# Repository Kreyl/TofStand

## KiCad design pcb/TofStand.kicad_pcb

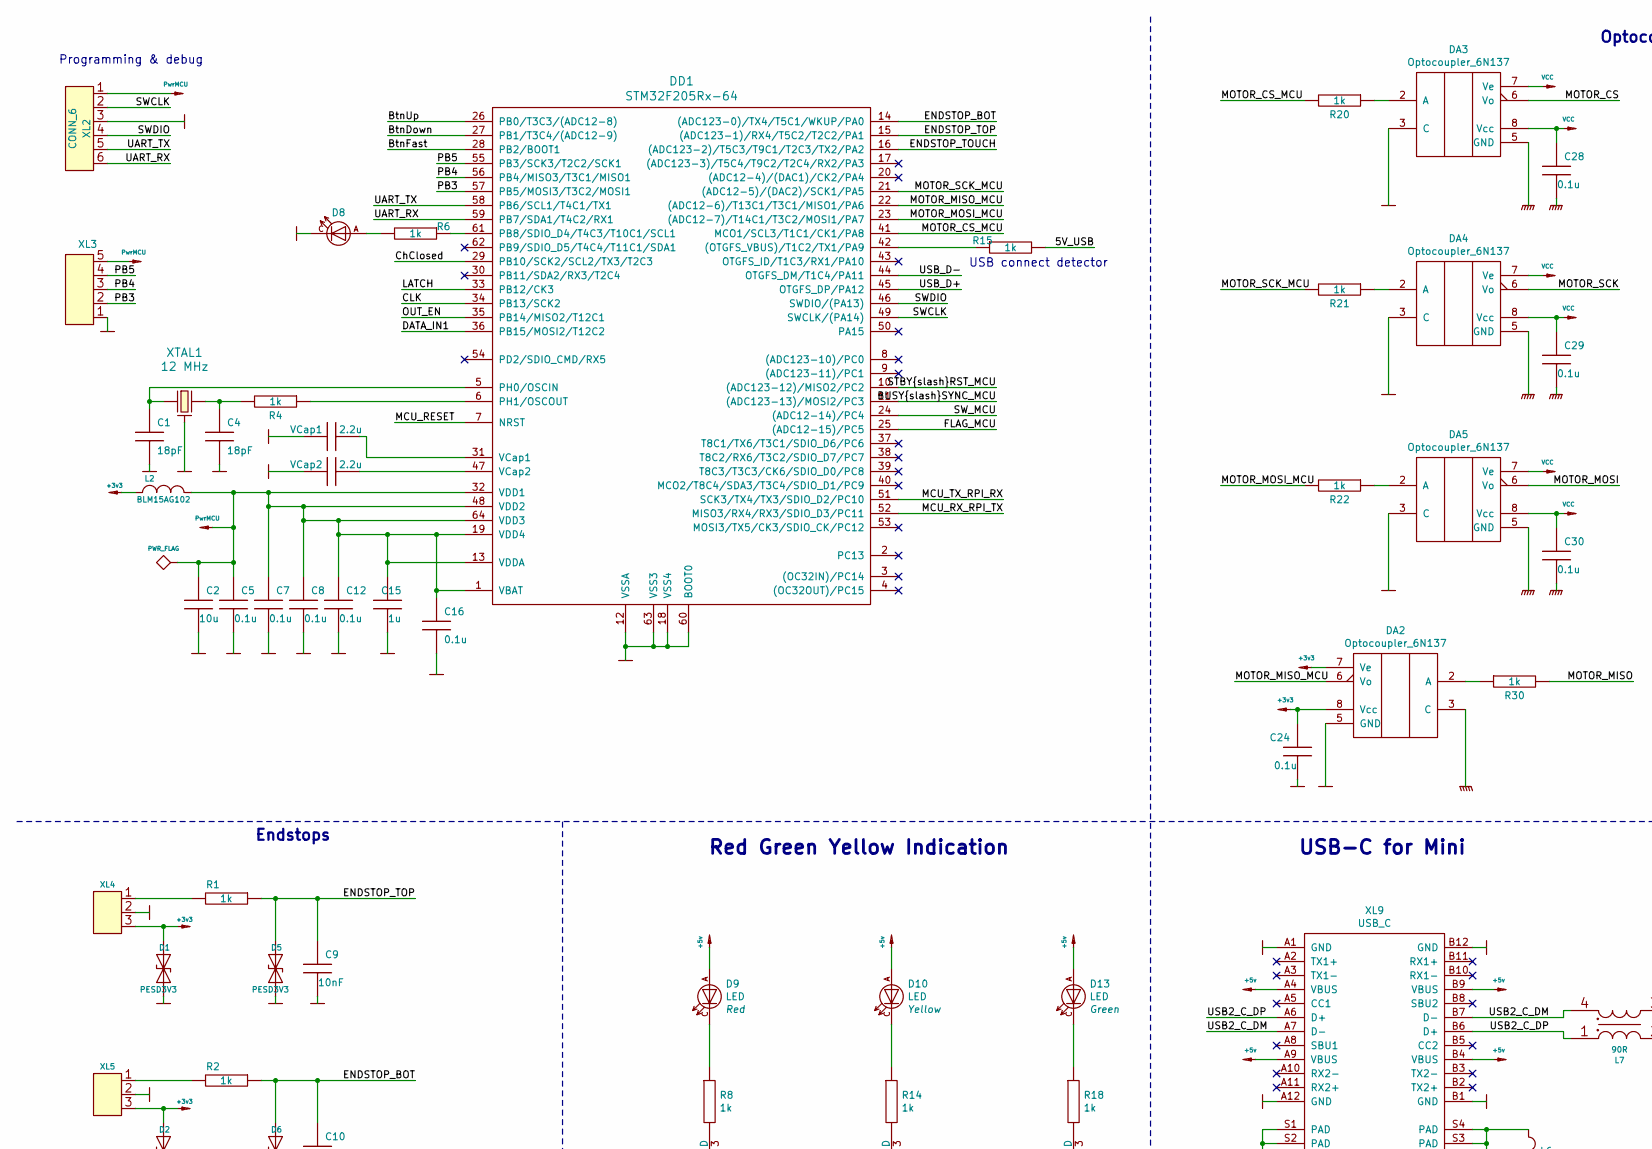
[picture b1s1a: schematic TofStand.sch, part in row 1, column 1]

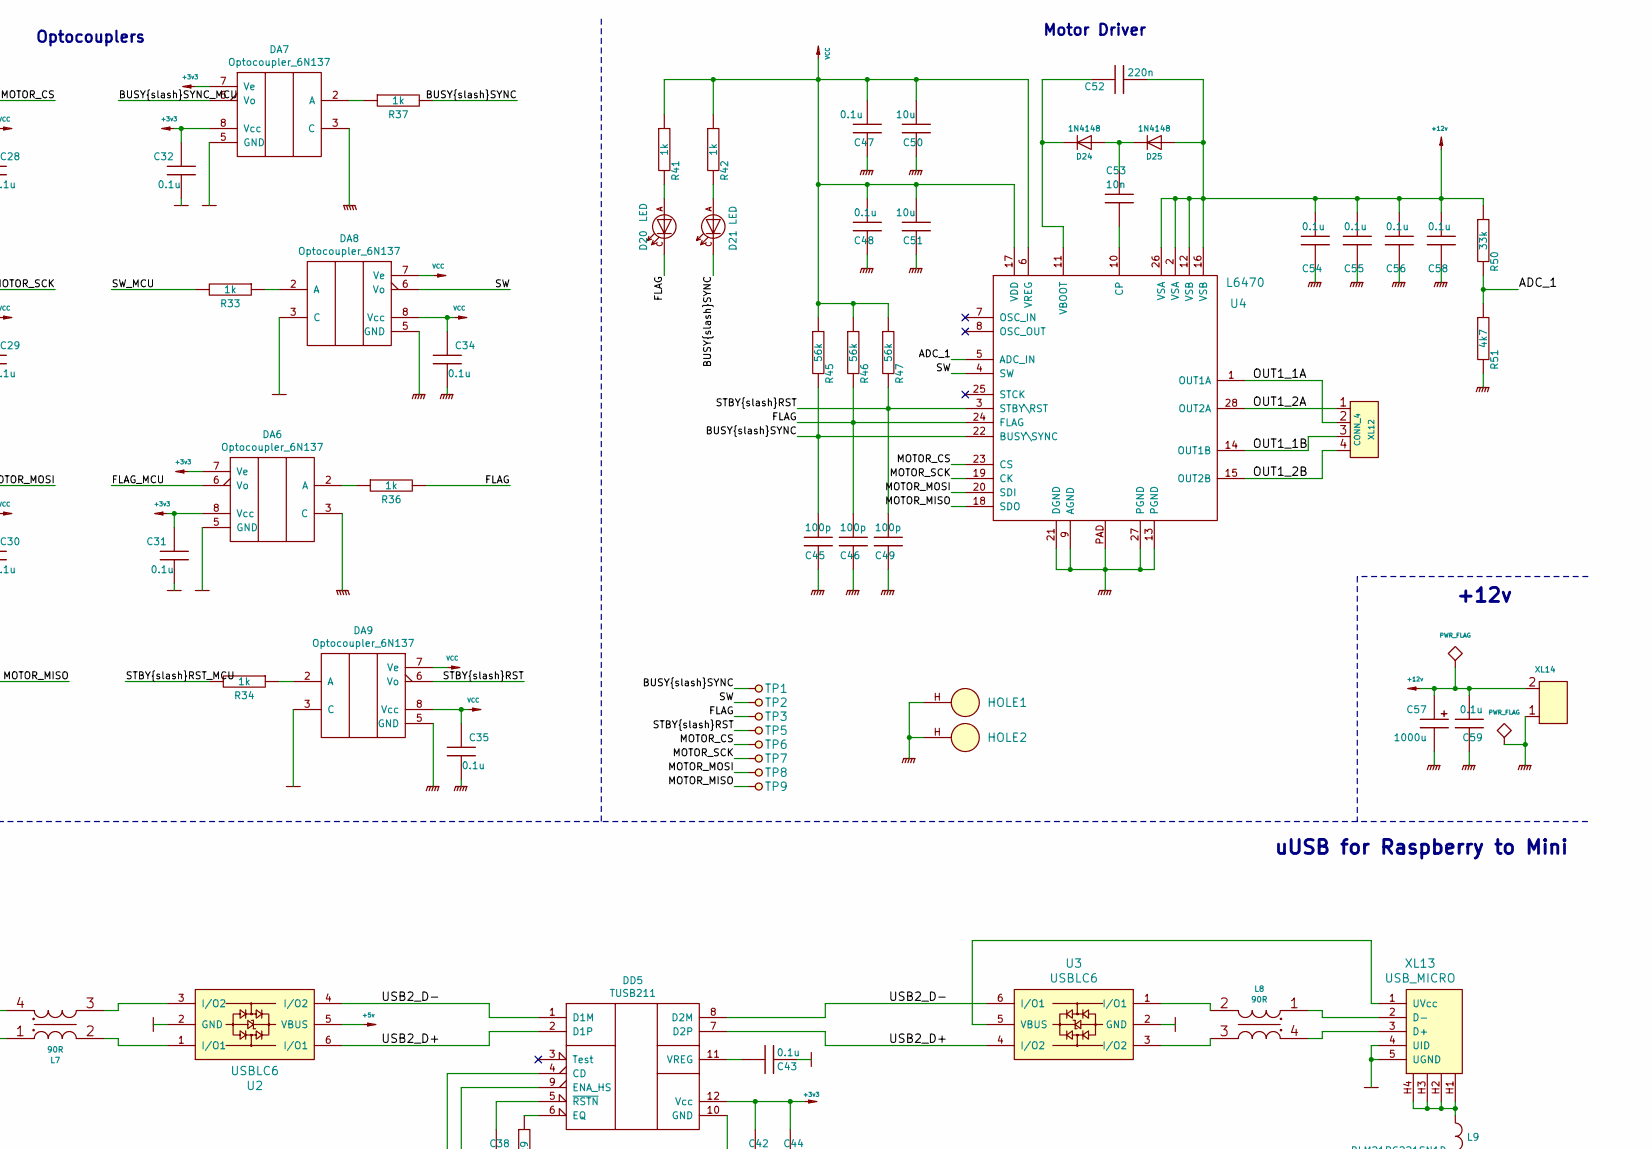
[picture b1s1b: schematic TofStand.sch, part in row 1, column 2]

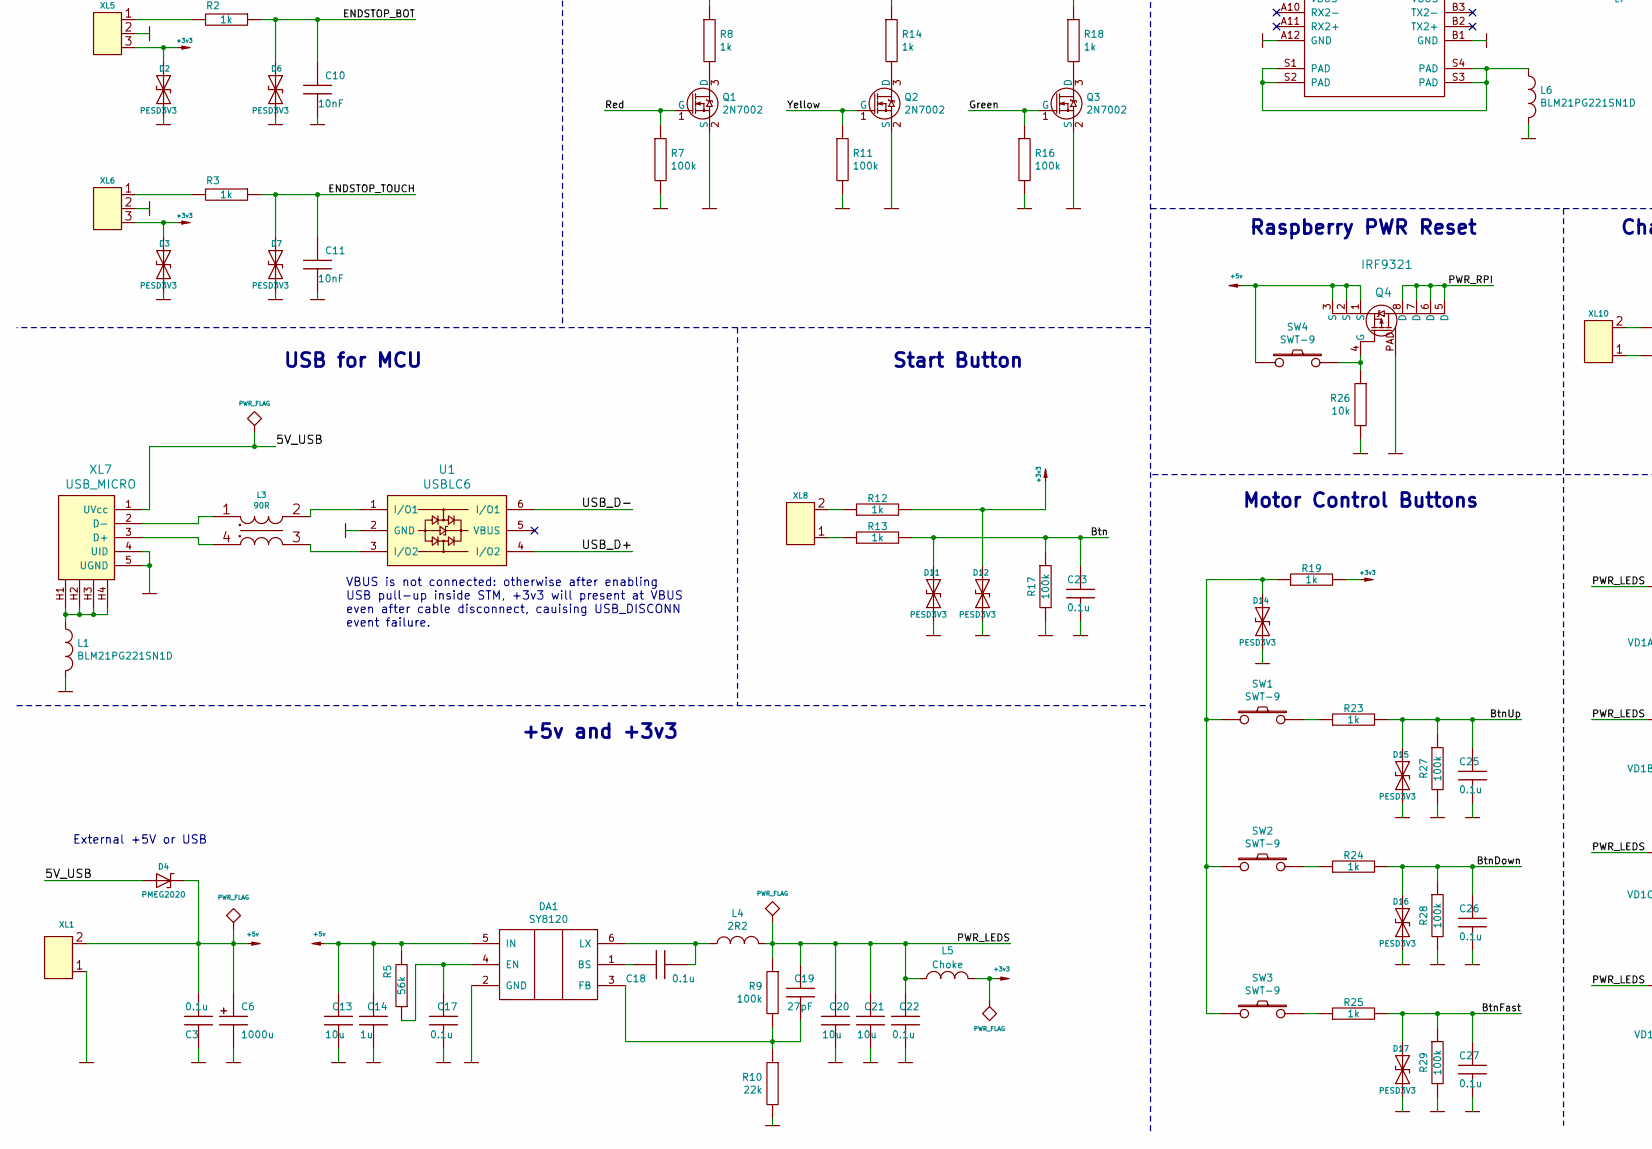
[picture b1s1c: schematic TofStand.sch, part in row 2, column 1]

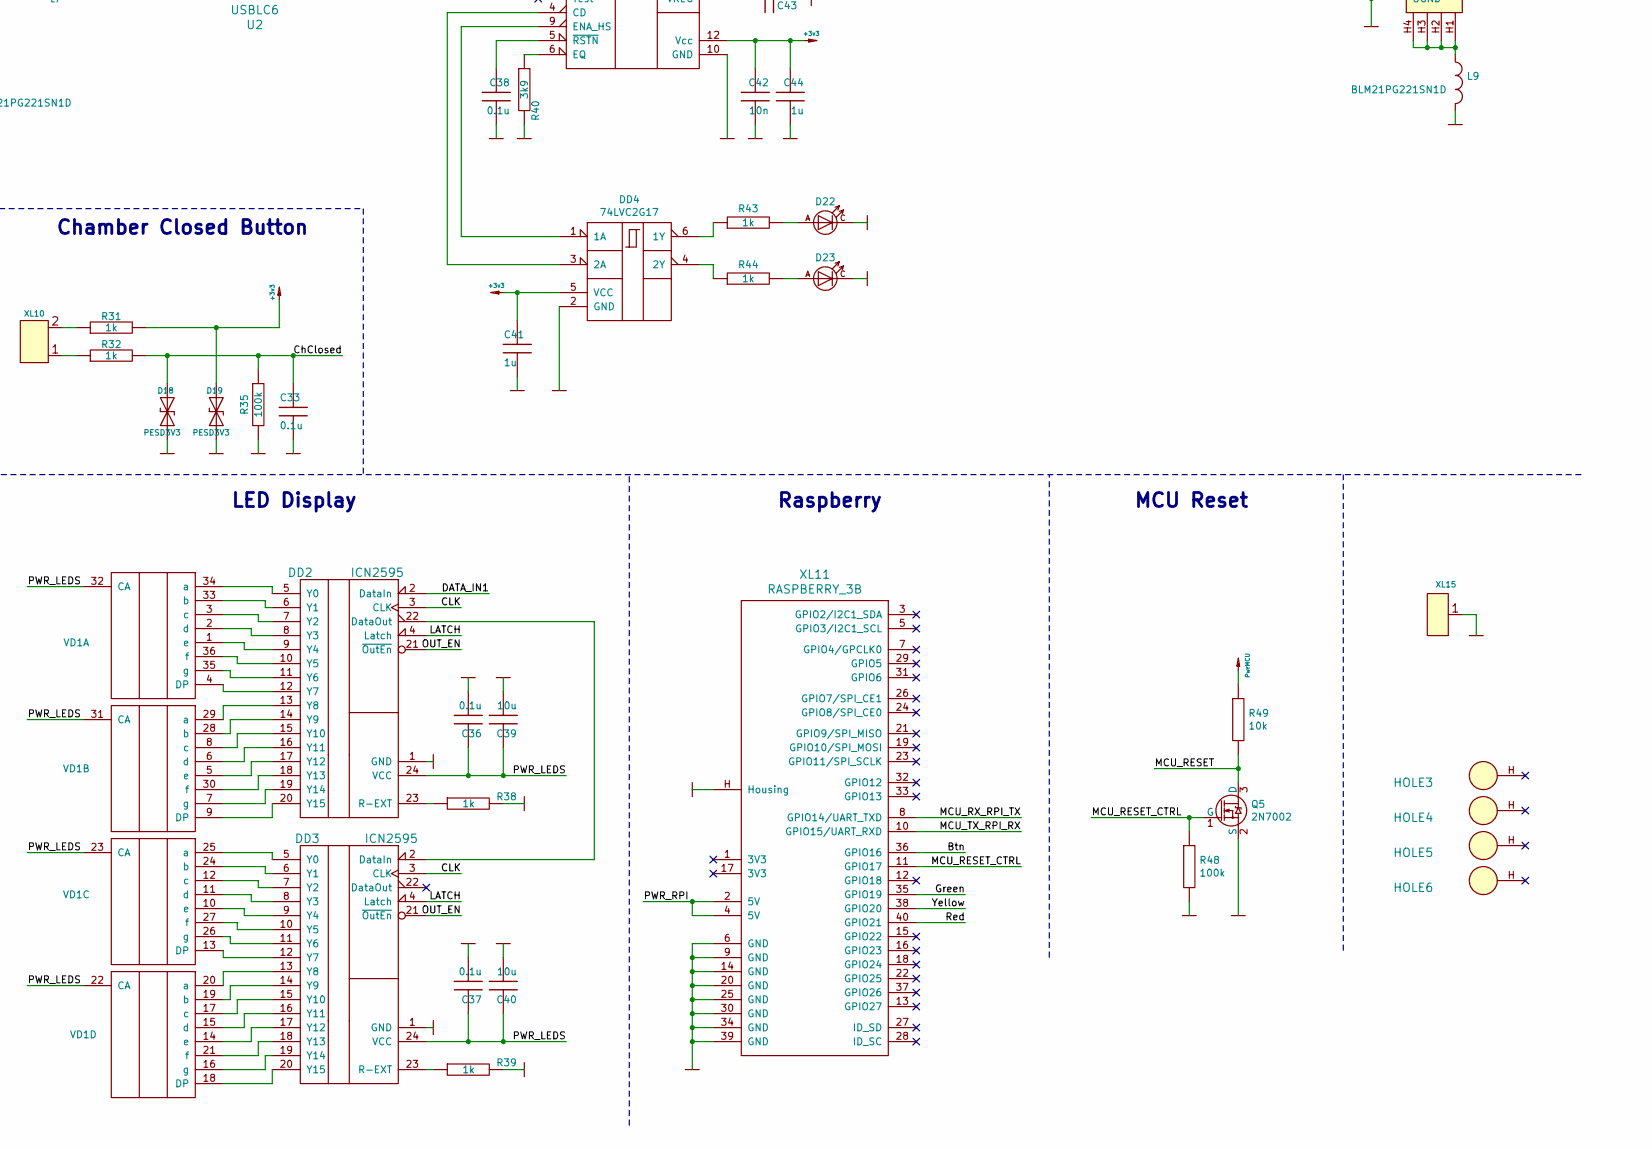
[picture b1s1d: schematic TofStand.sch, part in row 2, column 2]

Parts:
C1, C4: 18pF; CAP_0603_Silks
C2, C13, C20, C21, C39, C40, C50, C51: 10u; CAP_0805
C3, C5, C7, C8, C12, C16, C17, C18, C22, C23, C24, C25, C26, C27, C28, C29, C30, C31, C32, C33, C34, C35, C36, C37, C38, C43, C47, C48, C54, C55, C56, C58, C59: 0.1u; CAP_0603_Silks
C6, C57: 1000u; CAP_10xxR
C9, C10, C11: 10nF; CAP_0603_Silks
C14, C15, C41, C44: 1u; CAP_0603_Silks
C19: 27pF; CAP_0603_Silks
C42, C53: 10n; CAP_0603_Silks
C45, C46, C49: 100p; CAP_0603_Silks
C52: 220n; CAP_0603_Silks
D1, D2, D3, D5, D6, D7, D11, D12, D14, D15, D16, D17, D18, D19: PESD3V3; SOD323
D4: PMEG2020; SOD323
D8, D20, D21, D22, D23: LED; LED_0603
D9, D10, D13: LED; LED_Through-Hole-5mm
D24, D25: 1N4148; SOD80C
DA1: SY8120; SOT23-6
DA2, DA3, DA4, DA5, DA6, DA7, DA8, DA9: Optocoupler_6N137; DIP-8_296_ELL
DD1: STM32F205Rx-64; LQFP64
DD2, DD3: ICN2595; TSSOP24_150_0635
DD4: 74LVC2G17; SOT23-6
DD5: TUSB211; X2QFN_12
HOLE1, HOLE2, HOLE3, HOLE4, HOLE5, HOLE6: HOLE_METALLED; Hole3_5_out6mm
L1, L6, L9: BLM21PG221SN1D; IND_0603
L2: BLM15AG102; IND_0402
L3, L7, L8: 90R; DLW21SN
L4: 2R2; IND_1515
L5: Choke; IND_0402
Q1, Q2, Q3, Q5: 2N7002; SOT23-3
Q4: IRF9321; SO8HEATSINK
R1, R2, R3, R4, R6, R8, R12, R13, R14, R15, R18, R19, R20, R21, R22, R23, R24, R25, R30, R31, R32, R33, R34, R36, R37, R38, R39, R41, R42, R43, R44: 1k; RES_0603
R5, R45, R46, R47: 56k; RES_0603
R7, R9, R11, R16, R17, R27, R28, R29, R35, R48: 100k; RES_0603
R10: 22k; RES_0603
R26, R49: 10k; RES_0603
R40: 3k9; RES_0603
R50: 33k; RES_0603
R51: 4k7; RES_0603
SW1, SW2, SW3, SW4: SWT-9; BTN_SWT9
TP1, TP2, TP3, TP5, TP6, TP7, TP8, TP9: TESTPOINT; TESTPOINT_1MM
U1, U2, U3: USBLC6; SOT23-6
U4: L6470; HTSSOP28
VCap1, VCap2: 2.2u; CAP_0603_Silks
VD1: 7SEGx4_CA; 7Segx4
XL1, XL14: CONN_2; 2ZHDRC-02P
XL2: CONN_6; PLS-6_LOCK
XL3: CONN_5; PLS-5
XL4, XL5, XL6: CONN_3; W03_Pitch_2d54
XL7, XL13: USB_MICRO; USBmicro_MOLEX_1050170001
XL8, XL10: CONN_2; WB-02(MW-2M)
XL9: USB_C; USB_C_MOLEX_1054500101
XL11: RASPBERRY_3B; RaspberryPi3
XL12: CONN_4; TermiBlockHeader_508_x4_R
XL15: CONN_1; PLS-1Rnd
XTAL1: 12 MHz; 03225C4

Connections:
+3v3: C24.1, C31.1, C32.1, C41.2, C42.2, C44.2, D1.C, D2.C, D3.C, D12.C, D19.C, DA2.7 (Ve), DA2.8 (Vcc), DA6.7 (Ve), DA6.8 (Vcc), DA7.7 (Ve), DA7.8 (Vcc), DD4.5 (VCC), DD5.12 (Vcc), L2.2, L5.1, R12.2, R19.2, R31.2, XL4.3, XL5.3, XL6.3
+5v: C3.1, C6.1, C13.1, C14.1, D4.C, D9.A, D10.A, D13.A, DA1.5 (IN), Q4.1 (S), Q4.2 (S), Q4.3 (S), R5.2, SW4.1, U2.5 (VBUS), XL1.2 (PM), XL9.A4 (VBUS), XL9.A9 (VBUS), XL9.B4 (VBUS), XL9.B9 (VBUS)
+12v: C52.2, C54.1, C55.1, C56.1, C57.1, C58.1, C59.1, D25.A, R50.1, U4.2 (VSA), U4.12 (VSB), U4.16 (VSB), U4.26 (VSA), XL14.2 (PM)
/5V_USB: D4.A, R15.2, XL7.1 (UVcc)
/ADC_1: R50.2, R51.1, U4.5 (ADC_IN)
/BUSY/SYNC: C45.1, D21.C, R37.2, R45.2, TP1.1, U4.22 (BUSY\SYNC)
/BUSY/SYNC_MCU: DA7.6 (Vo), DD1.11 ((ADC123-13)/MOSI2/PC3)
/Btn: C23.1, D11.C, R13.2, R17.1, XL11.36 (GPIO16)
/BtnDown: C26.1, D16.C, DD1.27 (PB1/T3C4/(ADC12-9)), R24.2, R28.1
/BtnFast: C27.1, D17.C, DD1.28 (PB2/BOOT1), R25.2, R29.1
/BtnUp: C25.1, D15.C, DD1.26 (PB0/T3C3/(ADC12-8)), R23.2, R27.1
/CLK: DD1.34 (PB13/SCK2), DD2.3 (CLK), DD3.3 (CLK)
/ChClosed: C33.1, D18.C, DD1.29 (PB10/SCK2/SCL2/TX3/T2C3), R32.2, R35.1
/DATA_IN1: DD1.36 (PB15/MOSI2/T12C2), DD2.2 (DataIn)
/ENDSTOP_BOT: C10.1, D6.C, DD1.14 ((ADC123-0)/TX4/T5C1/WKUP/PA0), R2.1
/ENDSTOP_TOP: C9.1, D5.C, DD1.15 ((ADC123-1)/RX4/T5C2/T2C2/PA1), R1.1
/ENDSTOP_TOUCH: C11.1, D7.C, DD1.16 ((ADC123-2)/T5C3/T9C1/T2C3/TX2/PA2), R3.1
/FLAG: C46.1, D20.C, R36.2, R46.2, TP3.1, U4.24 (FLAG)
/FLAG_MCU: DA6.6 (Vo), DD1.25 ((ADC12-15)/PC5)
/Green: Q3.1 (G), R16.1, XL11.35 (GPIO19)
/LATCH: DD1.33 (PB12/CK3), DD2.4 (Latch), DD3.4 (Latch)
/MCU_RESET: DD1.7 (NRST), Q5.3 (D), R49.2
/MCU_RESET_CTRL: Q5.1 (G), R48.1, XL11.11 (GPIO17)
/MCU_RX_RPI_TX: DD1.52 (MISO3/RX4/RX3/SDIO_D3/PC11), XL11.8 (GPIO14/UART_TXD)
/MCU_TX_RPI_RX: DD1.51 (SCK3/TX4/TX3/SDIO_D2/PC10), XL11.10 (GPIO15/UART_RXD)
/MOTOR_CS: DA3.6 (Vo), TP6.1, U4.23 (CS)
/MOTOR_CS_MCU: DD1.41 (MCO1/SCL3/T1C1/CK1/PA8), R20.2
/MOTOR_MISO: R30.2, TP9.1, U4.18 (SDO)
/MOTOR_MISO_MCU: DA2.6 (Vo), DD1.22 ((ADC12-6)/T13C1/T3C1/MISO1/PA6)
/MOTOR_MOSI: DA5.6 (Vo), TP8.1, U4.20 (SDI)
/MOTOR_MOSI_MCU: DD1.23 ((ADC12-7)/T14C1/T3C2/MOSI1/PA7), R22.2
/MOTOR_SCK: DA4.6 (Vo), TP7.1, U4.19 (CK)
/MOTOR_SCK_MCU: DD1.21 ((ADC12-5)/(DAC2)/SCK1/PA5), R21.2
/OUT1_1A: U4.1 (OUT1A), XL12.2 (PM)
/OUT1_1B: U4.14 (OUT1B), XL12.3
/OUT1_2A: U4.28 (OUT2A), XL12.1
/OUT1_2B: U4.15 (OUT2B), XL12.4
/OUT_EN: DD1.35 (PB14/MISO2/T12C1), DD2.21 (~OutEn), DD3.21 (~OutEn)
/PB3: DD1.57 (PB5/MOSI3/T3C2/MOSI1), XL3.2
/PB4: DD1.56 (PB4/MISO3/T3C1/MISO1), XL3.3
/PB5: DD1.55 (PB3/SCK3/T2C2/SCK1), XL3.4
/PWR_LEDS: C19.1, C20.1, C21.1, C22.1, C36.2, C37.2, C39.2, C40.2, DD2.24 (VCC), DD3.24 (VCC), L4.2, L5.2, R9.1, VD1.22 (CA), VD1.23 (CA), VD1.31 (CA), VD1.32 (CA)
/PWR_RPI: Q4.5 (D), Q4.6 (D), Q4.7 (D), Q4.8 (D), XL11.2 (5V), XL11.4 (5V)
/Red: Q1.1 (G), R7.1, XL11.40 (GPIO21)
/STBY/RST: C49.1, DA9.6 (Vo), R47.2, TP5.1, U4.3 (STBY\RST)
/STBY/RST_MCU: DD1.10 ((ADC123-12)/MISO2/PC2), R34.2
/SW: DA8.6 (Vo), TP2.1, U4.4 (SW)
/SWCLK: DD1.49 (SWCLK/(PA14)), XL2.2
/SWDIO: DD1.46 (SWDIO/(PA13)), XL2.4
/SW_MCU: DD1.24 ((ADC12-14)/PC4), R33.2
/UART_RX: DD1.59 (PB7/SDA1/T4C2/RX1), XL2.6
/UART_TX: DD1.58 (PB6/SCL1/T4C1/TX1), XL2.5
/USB2_C_DM: L7.4, XL9.A7 (D-), XL9.B7 (D-)
/USB2_C_DP: L7.1, XL9.A6 (D+), XL9.B6 (D+)
/USB2_D+: DD5.2 (D1P), DD5.7 (D2P), U2.6 (I/O1), U3.4 (I/O2)
/USB2_D-: DD5.1 (D1M), DD5.8 (D2M), U2.4 (I/O2), U3.6 (I/O1)
/USB_D+: DD1.45 (OTGFS_DP/PA12), U1.4 (I/O2)
/USB_D-: DD1.44 (OTGFS_DM/T1C4/PA11), U1.6 (I/O1)
/Yellow: Q2.1 (G), R11.1, XL11.38 (GPIO20)
GND: C1.2, C2.2, C3.2, C4.2, C5.2, C6.2, C7.2, C8.2, C9.2, C10.2, C11.2, C12.2, C13.2, C14.2, C15.2, C16.2, C17.2, C20.2, C21.2, C22.2, C23.2, C24.2, C25.2, C26.2, C27.2, C31.2, C32.2, C33.2, C36.1, C37.1, C38.1, C39.1, C40.1, C41.1, C42.1, C43.1, C44.1, D1.A, D2.A, D3.A, D5.A, D6.A, D7.A, D8.C, D11.A, D12.A, D14.A, D15.A, D16.A, D17.A, D18.A, D19.A, D22.C, D23.C, DA1.2 (GND), DA2.5 (GND), DA3.3 (C), DA4.3 (C), DA5.3 (C), DA6.5 (GND), DA7.5 (GND), DA8.3 (C), DA9.3 (C), DD1.12 (VSSA), DD1.18 (VSS4), DD1.60 (BOOT0), DD1.63 (VSS3), DD2.1 (GND), DD3.1 (GND), DD4.2 (GND), DD5.10 (GND), L1.2, L6.2, L9.2, Q1.2 (S), Q2.2 (S), Q3.2 (S), Q4.PAD, Q5.2 (S), R7.2, R10.2, R11.2, R16.2, R17.2, R26.2, R27.2, R28.2, R29.2, R35.2, R38.2, R39.2, R40.2, R48.2, U1.2 (GND), U2.2 (GND), U3.2 (GND), VCap1.2, VCap2.2, XL1.1, XL2.3, XL3.1, XL4.2 (PM), XL5.2 (PM), XL6.2 (PM), XL7.4 (UID), XL7.5 (UGND), XL9.A1 (GND), XL9.A12 (GND), XL9.B1 (GND), XL9.B12 (GND), XL11.6 (GND), XL11.9 (GND), XL11.14 (GND), XL11.20 (GND), XL11.25 (GND), XL11.30 (GND), XL11.34 (GND)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
GNDPWR: C28.2, C29.2, C30.2, C34.2, C35.2, C45.2, C46.2, C47.2, C48.2, C49.2, C50.2, C51.2, C54.2, C55.2, C56.2, C57.2, C58.2, C59.2, DA2.3 (C), DA3.5 (GND), DA4.5 (GND), DA5.5 (GND), DA6.3 (C), DA7.3 (C), DA8.5 (GND), DA9.5 (GND), HOLE1.H, HOLE2.H, R51.2, U4.9 (AGND), U4.13 (PGND), U4.21 (DGND), U4.27 (PGND), U4.PAD, XL14.1
unnamed: C1.1, DD1.5 (PH0/OSCIN), XTAL1.1
unnamed: C4.1, R4.2, XTAL1.2
unnamed: C17.1, DA1.4 (EN), R5.1
unnamed: C18.1, DA1.1 (BS)
unnamed: C18.2, DA1.6 (LX), L4.1
unnamed: C19.2, DA1.3 (FB), R9.2, R10.1
unnamed: C52.1, D24.C, U4.11 (VBOOT)
unnamed: C53.1, D24.A, D25.C
unnamed: C53.2, U4.10 (CP)
unnamed: C38.2, DD5.5 (~RSTN)
unnamed: C43.2, DD5.11 (VREG)
unnamed: D8.A, R6.2
unnamed: D9.C, R8.1
unnamed: D10.C, R14.1
unnamed: D13.C, R18.1
unnamed: D14.C, R19.1, SW1.1, SW2.1, SW3.1
unnamed: D20.A, R41.2
unnamed: D21.A, R42.2
unnamed: D22.A, R43.2
unnamed: D23.A, R44.2
unnamed: DA2.2 (A), R30.1
unnamed: DA3.2 (A), R20.1
unnamed: DA4.2 (A), R21.1
unnamed: DA5.2 (A), R22.1
unnamed: DA6.2 (A), R36.1
unnamed: DA7.2 (A), R37.1
unnamed: DA8.2 (A), R33.1
unnamed: DA9.2 (A), R34.1
unnamed: DD1.6 (PH1/OSCOUT), R4.1
unnamed: DD1.31 (VCap1), VCap1.1
unnamed: DD1.42 ((OTGFS_VBUS)/T1C2/TX1/PA9), R15.1
unnamed: DD1.47 (VCap2), VCap2.1
unnamed: DD1.61 (PB8/SDIO_D4/T4C3/T10C1/SCL1), R6.1
unnamed: DD2.22 (DataOut), DD3.2 (DataIn)
unnamed: DD3.5 (Y0), VD1.25 (a)
unnamed: DD3.6 (Y1), VD1.24 (b)
unnamed: DD3.7 (Y2), VD1.12 (c)
unnamed: DD3.8 (Y3), VD1.11 (d)
unnamed: DD3.9 (Y4), VD1.10 (e)
unnamed: DD3.10 (Y5), VD1.27 (f)
unnamed: DD3.11 (Y6), VD1.26 (g)
unnamed: DD3.12 (Y7), VD1.13 (DP)
unnamed: DD3.13 (Y8), VD1.20 (a)
unnamed: DD3.14 (Y9), VD1.19 (b)
unnamed: DD3.15 (Y10), VD1.17 (c)
unnamed: DD3.16 (Y11), VD1.15 (d)
unnamed: DD3.17 (Y12), VD1.14 (e)
unnamed: DD3.18 (Y13), VD1.21 (f)
unnamed: DD3.19 (Y14), VD1.16 (g)
unnamed: DD3.20 (Y15), VD1.18 (DP)
unnamed: DD3.23 (R-EXT), R39.1
unnamed: DD4.1 (1A), DD5.9 (ENA_HS)
unnamed: DD4.3 (2A), DD5.4 (CD)
unnamed: DD4.4 (2Y), R44.1
unnamed: DD2.5 (Y0), VD1.34 (a)
unnamed: DD4.6 (1Y), R43.1
unnamed: DD2.6 (Y1), VD1.33 (b)
unnamed: DD2.7 (Y2), VD1.3 (c)
unnamed: DD2.8 (Y3), VD1.2 (d)
unnamed: DD2.9 (Y4), VD1.1 (e)
unnamed: DD2.10 (Y5), VD1.36 (f)
unnamed: DD2.11 (Y6), VD1.35 (g)
unnamed: DD2.12 (Y7), VD1.4 (DP)
unnamed: DD2.13 (Y8), VD1.29 (a)
unnamed: DD2.14 (Y9), VD1.28 (b)
unnamed: DD2.15 (Y10), VD1.8 (c)
unnamed: DD2.16 (Y11), VD1.6 (d)
unnamed: DD2.17 (Y12), VD1.5 (e)
unnamed: DD2.18 (Y13), VD1.30 (f)
unnamed: DD2.19 (Y14), VD1.7 (g)
unnamed: DD2.20 (Y15), VD1.9 (DP)
unnamed: DD2.23 (R-EXT), R38.1
unnamed: DD5.6 (EQ), R40.1
unnamed: L3.1, XL7.2 (D-)
unnamed: L1.1, XL7.H1, XL7.H2, XL7.H3, XL7.H4
unnamed: L3.2, U1.1 (I/O1)
unnamed: L3.3, U1.3 (I/O2)
unnamed: L3.4, XL7.3 (D+)
unnamed: L6.1, XL9.S1 (PAD), XL9.S2 (PAD), XL9.S3 (PAD), XL9.S4 (PAD)
unnamed: L7.2, U2.1 (I/O1)
unnamed: L7.3, U2.3 (I/O2)
unnamed: L8.1, XL13.2 (D-)
unnamed: L8.2, U3.1 (I/O1)
unnamed: L8.3, U3.3 (I/O2)
unnamed: L8.4, XL13.3 (D+)
unnamed: L9.1, XL13.H1, XL13.H2, XL13.H3, XL13.H4
unnamed: Q1.3 (D), R8.2
unnamed: Q2.3 (D), R14.2
unnamed: Q3.3 (D), R18.2
unnamed: Q4.4 (G), R26.1, SW4.2
unnamed: R1.2, XL4.1
unnamed: R2.2, XL5.1
unnamed: R3.2, XL6.1
unnamed: R13.1, XL8.1
unnamed: R12.1, XL8.2 (PM)
unnamed: R23.1, SW1.2
unnamed: R24.1, SW2.2
unnamed: R25.1, SW3.2
unnamed: R31.1, XL10.2 (PM)
unnamed: R32.1, XL10.1
unnamed: U3.5 (VBUS), XL13.1 (UVcc)
PwrMCU: C2.1, C5.1, C7.1, C8.1, C12.1, C15.1, C16.1, DD1.1 (VBAT), DD1.13 (VDDA), DD1.19 (VDD4), DD1.32 (VDD1), DD1.48 (VDD2), DD1.64 (VDD3), L2.1, R49.1, XL2.1, XL3.5
VCC: C28.1, C29.1, C30.1, C34.1, C35.1, C47.1, C48.1, C50.1, C51.1, DA3.7 (Ve), DA3.8 (Vcc), DA4.7 (Ve), DA4.8 (Vcc), DA5.7 (Ve), DA5.8 (Vcc), DA8.7 (Ve), DA8.8 (Vcc), DA9.7 (Ve), DA9.8 (Vcc), R41.1, R42.1, R45.1, R46.1, R47.1, U4.6 (VREG), U4.17 (VDD)

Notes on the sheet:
VBUS is not connected: otherwise after enabling USB pull-up inside STM, +3v3 will present at VBUS even after cable disconnect, cauising USB_DISCONN event failure.
USB for MCU
USB connect detector
Programming & debug
Endstops
Red Green Yellow Indication
Optocouplers
Motor Driver
Start Button
uUSB for Raspberry to Mini
+5v and +3v3
USB-C for Mini
+12v
Motor Control Buttons
Raspberry
LED Display
MCU Reset
External +5V or USB
Raspberry PWR Reset
Chamber Closed Button

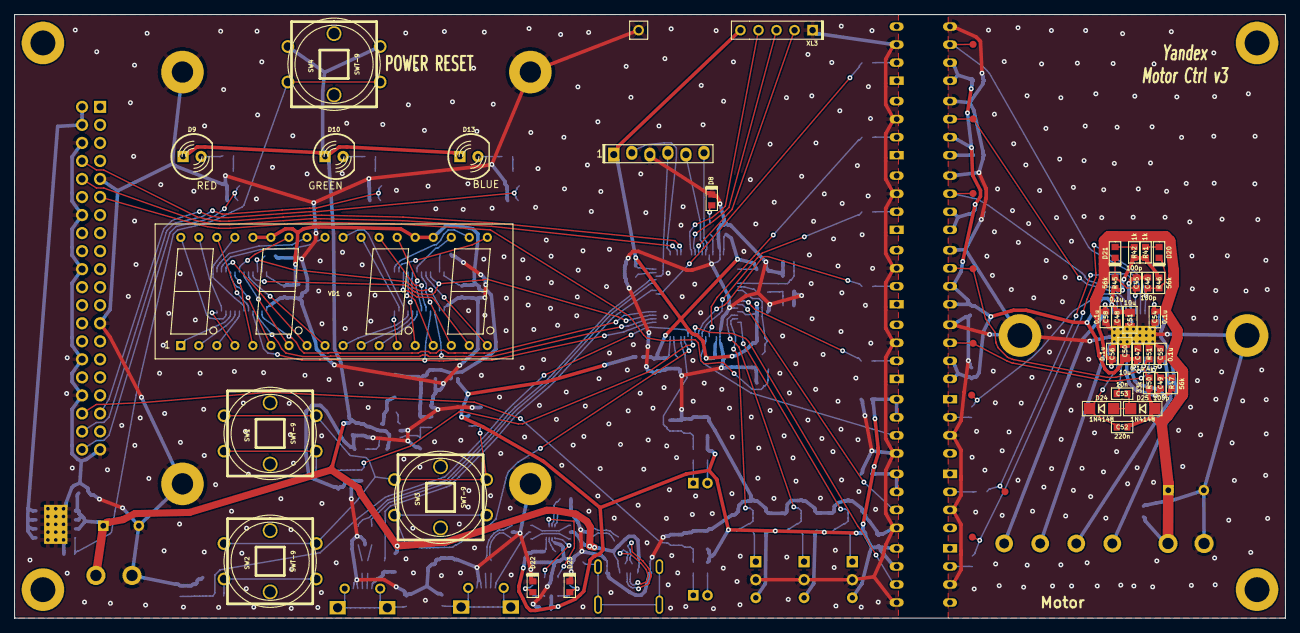
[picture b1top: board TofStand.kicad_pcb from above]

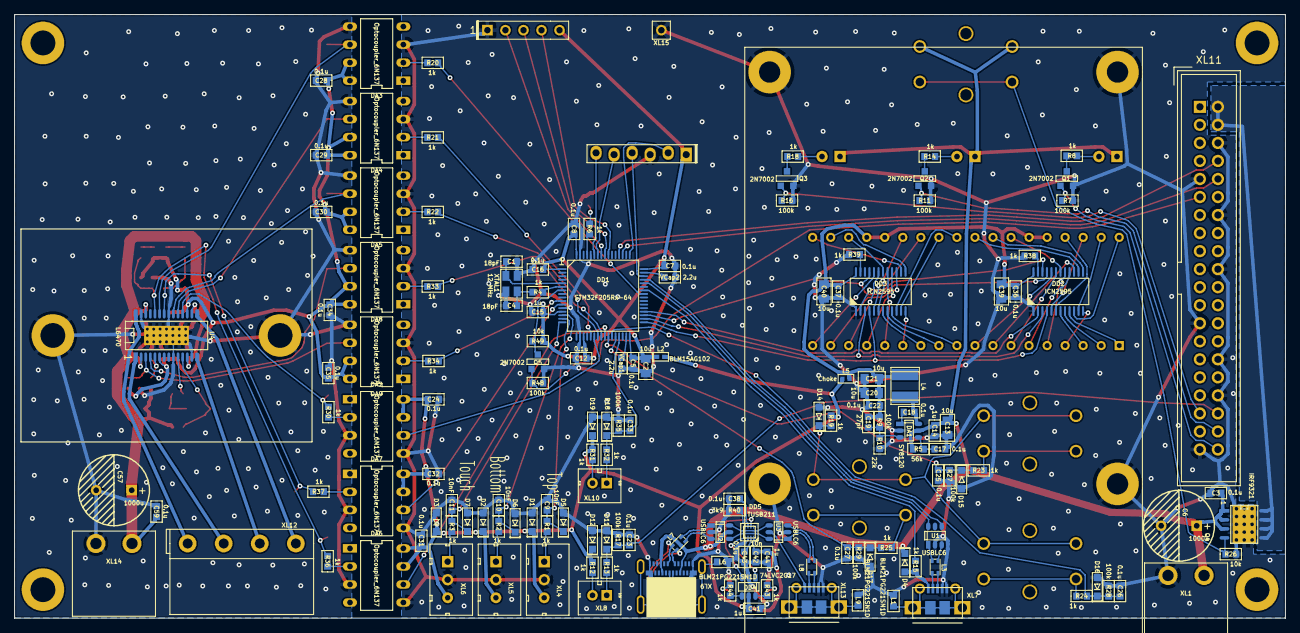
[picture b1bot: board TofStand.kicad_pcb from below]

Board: 2 copper layers, 179.0 x 85.0 mm, 204 parts (153 on the bottom side), 164 nets.

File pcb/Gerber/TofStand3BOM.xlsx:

Ref | Value | Footprint | Datasheet | Manufacturer | Vendor
C1 | 18pF | Capacitors:CAP_0603_Silks
C2 | 10u | Capacitors:CAP_0805
C3 | 0.1u | Capacitors:CAP_0603_Silks | ~
C4 | 18pF | Capacitors:CAP_0603_Silks
C5 | 0.1u | Capacitors:CAP_0603_Silks
C6 | 1000u | Capacitors:CAP_10xxR
C7 | 0.1u | Capacitors:CAP_0603_Silks
C8 | 0.1u | Capacitors:CAP_0603_Silks
C9 | 10nF | Capacitors:CAP_0603_Silks
C10 | 10nF | Capacitors:CAP_0603_Silks
C11 | 10nF | Capacitors:CAP_0603_Silks
C12 | 0.1u | Capacitors:CAP_0603_Silks
C13 | 10u | Capacitors:CAP_0805
C14 | 1u | Capacitors:CAP_0603_Silks
C15 | 1u | Capacitors:CAP_0603_Silks
C16 | 0.1u | Capacitors:CAP_0603_Silks
C17 | 0.1u | Capacitors:CAP_0603_Silks
C18 | 0.1u | Capacitors:CAP_0603_Silks
C19 | 27pF | Capacitors:CAP_0603_Silks
C20 | 10u | Capacitors:CAP_0805
C21 | 10u | Capacitors:CAP_0805
C22 | 0.1u | Capacitors:CAP_0603_Silks
C23 | 0.1u | Capacitors:CAP_0603_Silks
C24 | 0.1u | Capacitors:CAP_0603_Silks
C25 | 0.1u | Capacitors:CAP_0603_Silks
C26 | 0.1u | Capacitors:CAP_0603_Silks
C27 | 0.1u | Capacitors:CAP_0603_Silks
C28 | 0.1u | Capacitors:CAP_0603_Silks
C29 | 0.1u | Capacitors:CAP_0603_Silks
C30 | 0.1u | Capacitors:CAP_0603_Silks
C31 | 0.1u | Capacitors:CAP_0603_Silks
C32 | 0.1u | Capacitors:CAP_0603_Silks
C33 | 0.1u | Capacitors:CAP_0603_Silks
C34 | 0.1u | Capacitors:CAP_0603_Silks
C35 | 0.1u | Capacitors:CAP_0603_Silks
C36 | 0.1u | Capacitors:CAP_0603_Silks
C37 | 0.1u | Capacitors:CAP_0603_Silks
C38 | 0.1u | Capacitors:CAP_0603_Silks
C39 | 10u | Capacitors:CAP_0805
C40 | 10u | Capacitors:CAP_0805
C41 | 1u | Capacitors:CAP_0603_Silks
C42 | 10n | Capacitors:CAP_0603_Silks
C43 | 0.1u | Capacitors:CAP_0603_Silks
C44 | 1u | Capacitors:CAP_0603_Silks
C45 | 100p | Capacitors:CAP_0603_Silks | ~
C46 | 100p | Capacitors:CAP_0603_Silks | ~
C47 | 0.1u | Capacitors:CAP_0603_Silks | ~
C48 | 0.1u | Capacitors:CAP_0603_Silks | ~
C49 | 100p | Capacitors:CAP_0603_Silks | ~
C50 | 10u | Capacitors:CAP_0805 | ~
C51 | 10u | Capacitors:CAP_0805 | ~
C52 | 220n | Capacitors:CAP_0603_Silks | ~
C53 | 10n | Capacitors:CAP_0603_Silks | ~
C54 | 0.1u | Capacitors:CAP_0603_Silks | ~
C55 | 0.1u | Capacitors:CAP_0603_Silks | ~
C56 | 0.1u | Capacitors:CAP_0603_Silks | ~
C57 | 1000u | Capacitors:CAP_10xxR
C58 | 0.1u | Capacitors:CAP_0603_Silks | ~
C59 | 0.1u | Capacitors:CAP_0603_Silks | ~
D1 | PESD3V3 | Diodes:SOD323
D2 | PESD3V3 | Diodes:SOD323
D3 | PESD3V3 | Diodes:SOD323
D4 | PMEG2020 | Diodes:SOD323
D5 | PESD3V3 | Diodes:SOD323
D6 | PESD3V3 | Diodes:SOD323
D7 | PESD3V3 | Diodes:SOD323
D8 | LED | LEDs:LED_0603
D9 | LED | LEDs:LED_Through-Hole-5mm
D10 | LED | LEDs:LED_Through-Hole-5mm
D11 | PESD3V3 | Diodes:SOD323
D12 | PESD3V3 | Diodes:SOD323
D13 | LED | LEDs:LED_Through-Hole-5mm
D14 | PESD3V3 | Diodes:SOD323
D15 | PESD3V3 | Diodes:SOD323
D16 | PESD3V3 | Diodes:SOD323
D17 | PESD3V3 | Diodes:SOD323
D18 | PESD3V3 | Diodes:SOD323
D19 | PESD3V3 | Diodes:SOD323
D20 | LED | LEDs:LED_0603 | ~
D21 | LED | LEDs:LED_0603 | ~
D22 | LED | LEDs:LED_0603
D23 | LED | LEDs:LED_0603
D24 | 1N4148 | Diodes:SOD80C | ~
D25 | 1N4148 | Diodes:SOD80C | ~
DA1 | SY8120 | SOT:SOT23-6
DA2 | Optocoupler_6N137 | DIP:DIP-8_296_ELL
DA3 | Optocoupler_6N137 | DIP:DIP-8_296_ELL
DA4 | Optocoupler_6N137 | DIP:DIP-8_296_ELL
DA5 | Optocoupler_6N137 | DIP:DIP-8_296_ELL
DA6 | Optocoupler_6N137 | DIP:DIP-8_296_ELL
DA7 | Optocoupler_6N137 | DIP:DIP-8_296_ELL
DA8 | Optocoupler_6N137 | DIP:DIP-8_296_ELL
DA9 | Optocoupler_6N137 | DIP:DIP-8_296_ELL
DD1 | STM32F205Rx-64 | LQFP_TQFP:LQFP64
DD2 | ICN2595 | SO_DIL_TSSOP:TSSOP24_150_0635
DD3 | ICN2595 | SO_DIL_TSSOP:TSSOP24_150_0635
DD4 | 74LVC2G17 | SOT:SOT23-6
DD5 | TUSB211 | QFN_DFN:X2QFN_12
L1 | BLM21PG221SN1D | Inductors:IND_0603
L2 | BLM15AG102 | Inductors:IND_0402
L3 | 90R | Inductors:DLW21SN
L4 | 2R2 | Inductors:IND_1515
L5 | Choke | Inductors:IND_0402
L6 | BLM21PG221SN1D | Inductors:IND_0603
L7 | 90R | Inductors:DLW21SN
L8 | 90R | Inductors:DLW21SN
L9 | BLM21PG221SN1D | Inductors:IND_0603
Q1 | 2N7002 | SOT:SOT23-3
Q2 | 2N7002 | SOT:SOT23-3
Q3 | 2N7002 | SOT:SOT23-3
Q4 | IRF9321 | SO_DIL_TSSOP:SO8HEATSINK
Q5 | 2N7002 | SOT:SOT23-3
R1 | 1k | Resistors:RES_0603
R2 | 1k | Resistors:RES_0603
R3 | 1k | Resistors:RES_0603
R4 | 1k | Resistors:RES_0603
R5 | 56k | Resistors:RES_0603
R6 | 1k | Resistors:RES_0603
R7 | 100k | Resistors:RES_0603
R8 | 1k | Resistors:RES_0603
R9 | 100k | Resistors:RES_0603
R10 | 22k | Resistors:RES_0603
R11 | 100k | Resistors:RES_0603
R12 | 1k | Resistors:RES_0603
R13 | 1k | Resistors:RES_0603
R14 | 1k | Resistors:RES_0603
R15 | 1k | Resistors:RES_0603
R16 | 100k | Resistors:RES_0603
R17 | 100k | Resistors:RES_0603
R18 | 1k | Resistors:RES_0603
R19 | 1k | Resistors:RES_0603
R20 | 1k | Resistors:RES_0603
R21 | 1k | Resistors:RES_0603
R22 | 1k | Resistors:RES_0603
R23 | 1k | Resistors:RES_0603
R24 | 1k | Resistors:RES_0603
R25 | 1k | Resistors:RES_0603
R26 | 10k | Resistors:RES_0603
R27 | 100k | Resistors:RES_0603
R28 | 100k | Resistors:RES_0603
R29 | 100k | Resistors:RES_0603
R30 | 1k | Resistors:RES_0603
R31 | 1k | Resistors:RES_0603
R32 | 1k | Resistors:RES_0603
R33 | 1k | Resistors:RES_0603
R34 | 1k | Resistors:RES_0603
R35 | 100k | Resistors:RES_0603
R36 | 1k | Resistors:RES_0603
R37 | 1k | Resistors:RES_0603
R38 | 1k | Resistors:RES_0603
R39 | 1k | Resistors:RES_0603
R40 | 3k9 | Resistors:RES_0603
R41 | 1k | Resistors:RES_0603 | ~
R42 | 1k | Resistors:RES_0603 | ~
R43 | 1k | Resistors:RES_0603
R44 | 1k | Resistors:RES_0603
R45 | 56k | Resistors:RES_0603 | ~
R46 | 56k | Resistors:RES_0603 | ~
R47 | 56k | Resistors:RES_0603 | ~
R48 | 100k | Resistors:RES_0603
R49 | 10k | Resistors:RES_0603
R50 | 33k | Resistors:RES_0603 | ~
R51 | 4k7 | Resistors:RES_0603 | ~
SW1 | SWT-9 | BtnsSwitches:BTN_SWT9
SW2 | SWT-9 | BtnsSwitches:BTN_SWT9
SW3 | SWT-9 | BtnsSwitches:BTN_SWT9
SW4 | SWT-9 | BtnsSwitches:BTN_SWT9
U1 | USBLC6 | SOT:SOT23-6
U2 | USBLC6 | SOT:SOT23-6
U3 | USBLC6 | SOT:SOT23-6
U4 | L6470 | SO_DIL_TSSOP:HTSSOP28 | ~
VCap1 | 2.2u | Capacitors:CAP_0603_Silks
VCap2 | 2.2u | Capacitors:CAP_0603_Silks
VD1 | 7SEGx4_CA | Display:7Segx4 | https://static.chipdip.ru/lib/195/DOC000195290.pdf
XL1 | CONN_2 | Connectors:2ZHDRC-02P
XL2 | CONN_6 | Connectors:PLS-6_LOCK
XL3 | CONN_5 | Connectors:PLS-5
XL4 | CONN_3 | Connectors:W03_Pitch_2d54
XL5 | CONN_3 | Connectors:W03_Pitch_2d54
XL6 | CONN_3 | Connectors:W03_Pitch_2d54
XL7 | USB_MICRO | Connectors:USBmicro_MOLEX_1050170001
XL8 | CONN_2 | Connectors:WB-02(MW-2M)
XL9 | USB_C | Connectors:USB_C_MOLEX_1054500101
XL10 | CONN_2 | Connectors:WB-02(MW-2M)
XL11 | RASPBERRY_3B | Installation:RaspberryPi3
XL12 | CONN_4 | Connectors:TermiBlockHeader_508_x4_R | ~
XL13 | USB_MICRO | Connectors:USBmicro_MOLEX_1050170001
XL14 | CONN_2 | Connectors:2ZHDRC-02P
XL15 | CONN_1 | Connectors:PLS-1Rnd
XTAL1 | 12 MHz | Quartz:03225C4

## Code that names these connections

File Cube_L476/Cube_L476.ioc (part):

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Mcu.Name=STM32L476R(C-E-G)Tx
Mcu.Package=LQFP64
Mcu.UserName=STM32L476RCTx
PA0.Signal=GPIO_Input
PA1.Signal=GPIO_Input
PA11.Mode=Device_Only
PA11.Signal=USB_OTG_FS_DM
PA12.Mode=Device_Only
PA12.Signal=USB_OTG_FS_DP
PA13\ (JTMS-SWDIO).Mode=Serial_Wire
PA13\ (JTMS-SWDIO).Signal=SYS_JTMS-SWDIO
PA14\ (JTCK-SWCLK).Mode=Serial_Wire
PA14\ (JTCK-SWCLK).Signal=SYS_JTCK-SWCLK
PA2.Signal=GPIO_Input
PA5.Mode=Full_Duplex_Slave
PA5.Signal=SPI1_SCK
PA6.Mode=Full_Duplex_Slave
PA6.Signal=SPI1_MISO
PA7.Mode=Full_Duplex_Slave
PA7.Signal=SPI1_MOSI
PA8.Signal=GPIO_Output
PA9.Mode=Activate_VBUS
PA9.Signal=USB_OTG_FS_VBUS
PB0.Signal=GPIO_Input
PB1.Signal=GPIO_Input
PB10.Signal=GPIO_Input
PB12.Signal=GPIO_Output
PB13.Mode=TX_Only_Simplex_Unidirect_Master
PB13.Signal=SPI2_SCK
PB14.Signal=GPIO_Output
PB15.Mode=TX_Only_Simplex_Unidirect_Master
PB15.Signal=SPI2_MOSI
PB2.Signal=GPIO_Input
PB3\ (JTDO-TRACESWO).Signal=GPIO_Output
PB4\ (NJTRST).Signal=GPIO_Output
PB5.Signal=GPIO_Output
PB6.Mode=Asynchronous
PB6.Signal=USART1_TX
PB7.Mode=Asynchronous
PB7.Signal=USART1_RX
PB8.Signal=GPIO_Output
PC10.Mode=Asynchronous
PC10.Signal=UART4_TX
PC11.Mode=Asynchronous
PC11.Signal=UART4_RX
PC2.Signal=GPIO_Output
PC3.Signal=GPIO_Input
PC4.Signal=GPIO_Output
PC5.Signal=GPIO_Input
PH0-OSC_IN\ (PH0).Mode=HSE-External-Oscillator
PH0-OSC_IN\ (PH0).Signal=RCC_OSC_IN
PH1-OSC_OUT\ (PH1).Mode=HSE-External-Oscillator
PH1-OSC_OUT\ (PH1).Signal=RCC_OSC_OUT
RCC.HSE_VALUE=8000000
board=custom

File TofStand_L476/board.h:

/*
 * board.h
 *
 *  Created on: 05 08 2018
 *      Author: Kreyl
 */

#pragma once

// ==== General ====
#define BOARD_NAME          "ToFStand3"
#define APP_NAME            "ToFStand3"

// MCU type as defined in the ST header.
#define STM32L476xx

// Freq of external crystal if any. Leave it here even if not used.
#define CRYSTAL_FREQ_HZ         12000000

// OS timer settings
#define STM32_ST_IRQ_PRIORITY   2
#define STM32_ST_USE_TIMER      5
#define SYS_TIM_CLK             (Clk.APB1FreqHz)    // Timer 5 is clocked by APB1

//  Periphery
#define I2C1_ENABLED            FALSE
#define I2C2_ENABLED            FALSE
#define I2C3_ENABLED            FALSE
#define SIMPLESENSORS_ENABLED   TRUE
#define BUTTONS_ENABLED         TRUE

#define ADC_REQUIRED            FALSE
#define STM32_DMA_REQUIRED      TRUE    // Leave this macro name for OS

#if 1 // ========================== GPIO =======================================
// EXTI
#define INDIVIDUAL_EXTI_IRQ_REQUIRED    FALSE

// UART
#define UART_GPIO       GPIOB
#define UART_TX_PIN     6
#define UART_RX_PIN     7

#define UART_RPI_GPIO   GPIOC
#define UART_RPI_TX     10
#define UART_RPI_RX     11

// LED
#define LED_PIN         GPIOB, 8

// Buttons
#define BTN_UP_PIN      GPIOB, 0, pudPullDown
#define BTN_DOWN_PIN    GPIOB, 1, pudPullDown
#define BTN_FAST_PIN    GPIOB, 2, pudPullDown

// Sensors
#define CHAMBER_CLOSED_PIN  GPIOB, 10
#define USB_DETECT_PIN  GPIOA, 9, pudPullDown

// 7 segment
#define SEGS_SPI        SPI2
#define SEG_MOSI        GPIOB, 15, omPushPull, pudNone, AF5
#define SEG_CLK         GPIOB, 13, omPushPull, pudNone, AF5
#define SEG_DRV_LE      GPIOB, 12
#define SEG_DRV_OE      GPIOB, 14

// Endstops
#define ENDSTOP_TOP     GPIOA, 1
#define ENDSTOP_BOTTOM  GPIOA, 0
#define ENDSTOP_TOUCH   GPIOA, 2

#if 1 // ==== L6470 ====
#define M_SPI           SPI1
#define M_SPI_GPIO      GPIOA
#define M_SCK           5
#define M_MISO          6
#define M_MOSI          7
#define M_CS            8
#define M_SPI_AF        AF5

#define M_AUX_GPIO      GPIOC
#define M_BUSY_SYNC1    3
#define M_SW1           4
#define M_FLAG1         5
#define M_STBY_RST      2
#endif

// USB
#define USB_DM          GPIOA, 11
#define USB_DP          GPIOA, 12
#define USB_AF          AF10
#define BOARD_OTG_NOVBUSSENS    TRUE

#endif // GPIO


#if ADC_REQUIRED // ======================= Inner ADC ==========================
// Clock divider: clock is generated from the APB2
#define ADC_CLK_DIVIDER		adcDiv2

// ADC channels
#define ADC_BATTERY_CHNL 	14
// ADC_VREFINT_CHNL
#define ADC_CHANNELS        { ADC_BATTERY_CHNL, ADC_VREFINT_CHNL }
#define ADC_CHANNEL_CNT     2   // Do not use countof(AdcChannels) as preprocessor does not know what is countof => cannot check
#define ADC_SAMPLE_TIME     ast24d5Cycles
#define ADC_OVERSAMPLING_RATIO  64   // 1 (no oversampling), 2, 4, 8, 16, 32, 64, 128, 256
#endif

#if 1 // =========================== DMA =======================================
// ==== Uart ====
// Remap is made automatically if required
#define UART_DMA_TX     STM32_DMA_STREAM_ID(2, 6)
#define UART_DMA_RX     STM32_DMA_STREAM_ID(2, 7)
#define UART_DMA_CHNL   2
#define UART_DMA_TX_MODE(Chnl) (STM32_DMA_CR_CHSEL(Chnl) | DMA_PRIORITY_LOW | STM32_DMA_CR_MSIZE_BYTE | STM32_DMA_CR_PSIZE_BYTE | STM32_DMA_CR_MINC | STM32_DMA_CR_DIR_M2P | STM32_DMA_CR_TCIE)
#define UART_DMA_RX_MODE(Chnl) (STM32_DMA_CR_CHSEL(Chnl) | DMA_PRIORITY_MEDIUM | STM32_DMA_CR_MSIZE_BYTE | STM32_DMA_CR_PSIZE_BYTE | STM32_DMA_CR_MINC | STM32_DMA_CR_DIR_P2M | STM32_DMA_CR_CIRC)

#define UART_RPI_DMA_TX     STM32_DMA_STREAM_ID(2, 3)
#define UART_RPI_DMA_RX     STM32_DMA_STREAM_ID(2, 5)
#define UART_RPI_DMA_CHNL   2
#define UART_DMA_RPI_TX_MODE(Chnl) (STM32_DMA_CR_CHSEL(Chnl) | DMA_PRIORITY_LOW | STM32_DMA_CR_MSIZE_BYTE | STM32_DMA_CR_PSIZE_BYTE | STM32_DMA_CR_MINC | STM32_DMA_CR_DIR_M2P | STM32_DMA_CR_TCIE)
#define UART_RPI_DMA_RX_MODE(Chnl) (STM32_DMA_CR_CHSEL(Chnl) | DMA_PRIORITY_MEDIUM | STM32_DMA_CR_MSIZE_BYTE | STM32_DMA_CR_PSIZE_BYTE | STM32_DMA_CR_MINC | STM32_DMA_CR_DIR_P2M | STM32_DMA_CR_CIRC)

// ==== SPI ====
#define SEGS_SPI_DMA_TX STM32_DMA_STREAM_ID(1, 5)
#define SEGS_DMA_TX_CHNL   1
#define SEGS_DMA_TX_MODE  \
        (STM32_DMA_CR_CHSEL(SEGS_DMA_TX_CHNL) | \
        DMA_PRIORITY_LOW |     \
        STM32_DMA_CR_MSIZE_BYTE | \
        STM32_DMA_CR_PSIZE_BYTE | \
        STM32_DMA_CR_TCIE | \
        STM32_DMA_CR_MINC |    /* Mem pointer increase */  \
        STM32_DMA_CR_DIR_M2P   /* Mem to peripheral */ )

#endif // DMA

#if 1 // ========================== USART ======================================
#define PRINTF_FLOAT_EN FALSE
#define UART_TXBUF_SZ   4096
#define UART_RXBUF_SZ   99

#define UARTS_CNT       2

#define CMD_UART_PARAMS \
    USART1, UART_GPIO, UART_TX_PIN, UART_GPIO, UART_RX_PIN, \
    UART_DMA_TX, UART_DMA_RX, UART_DMA_TX_MODE(UART_DMA_CHNL), UART_DMA_RX_MODE(UART_DMA_CHNL), uartclkHSI

#define RPI_UART_PARAMS \
    UART4, UART_RPI_GPIO, UART_RPI_TX, UART_RPI_GPIO, UART_RPI_RX, \
    UART_RPI_DMA_TX, UART_RPI_DMA_RX, \
    UART_DMA_RPI_TX_MODE(UART_RPI_DMA_CHNL), UART_RPI_DMA_RX_MODE(UART_RPI_DMA_CHNL), uartclkHSI

#endif

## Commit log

2019-08-01 Uart works
2019-08-02 Working on USB
2019-08-02 + Usb works
2019-08-02 Integrating movement
2019-08-02 + Motor works ok
2019-08-02 Endstop logic implemented
2019-08-03 * SpeedMax limited to 72000 * Deceleration increased * Top and Bottom sensors set up properly RC
2019-08-05 * Stop mode changed to HOLD
2019-08-15 - "Home" cmd + Move to top position after power-on
2019-08-27 + Led + Delay
2019-08-28 + SetCurrent
2019-08-29 + Sch added + MoveUp/Movedown * Stop by switch
2019-08-29 - up/down
2019-08-30 Motor current increased in run mode
2019-08-30 New pcb started
2019-08-30 Proceeding
2019-09-06 PCB sent to factory
2019-09-06 + F103 + UART works
2019-09-06 I just have recalled that F103 requires another connection with USB, and .current PCB does not allow this.
2019-09-06 + PLL 48MHz
2019-09-07 + PB12 to switch USB Pullup on/off
2019-09-07 + PB12 to switch USB Pullup on/off + Usb works
2019-09-10 + SetCur cmd * Default current is 15 + IRQs work
2019-09-10 USB "Not recognized" issue fixed somehow
2019-09-10 Usb connect/disconnect managed using all three GPIO mode select.
2019-09-14 + Composite device works
2019-09-14 + Bootloader started Contains IWDG
2019-09-14 Bootloader found the file, wrote it to memory, jumped there. I.e. works ok. Only file deleting left to implement.
2019-09-15 + Boot: file unlink done, fixed bug with wrong buffer inside WriteMemory function. RC - F205 fw + Main fw: rst cmd
2019-09-15 + Several binaries with different DEFAULT_CURRENT
2019-09-16 + PCB v2 + Release firmwares
2019-09-16 + SetStep + SetAcc
2019-10-01 + Settings on flash
2019-10-15 - Old releases
2019-10-30 + V2.0 Sch done
2019-11-18 + FW ToF3 first compilation
2019-11-18 + Segment display
2019-11-18 Motor works ok
2019-11-19 + RPI Uart works
2019-11-19 Button driven motor
2019-11-20 + L476 code
2019-11-21 + USB MSD+CDC works + Onboard Flash-based filesys works
2019-11-21 + Endstops IRQs work
2019-11-25 Proceeding with business logic
2019-11-28 + logic graph
2019-12-03 + State machine works at first
2019-12-03 * OP->Open, C->Cal
2019-12-04 SPI mode switched, works ok
2019-12-04 No test logic, only up/down
2019-12-05 + Settings read done
2019-12-05 + Bootloader works
2019-12-05 + File erase works
2019-12-05 + Hex of bootloader - Hex of F103
